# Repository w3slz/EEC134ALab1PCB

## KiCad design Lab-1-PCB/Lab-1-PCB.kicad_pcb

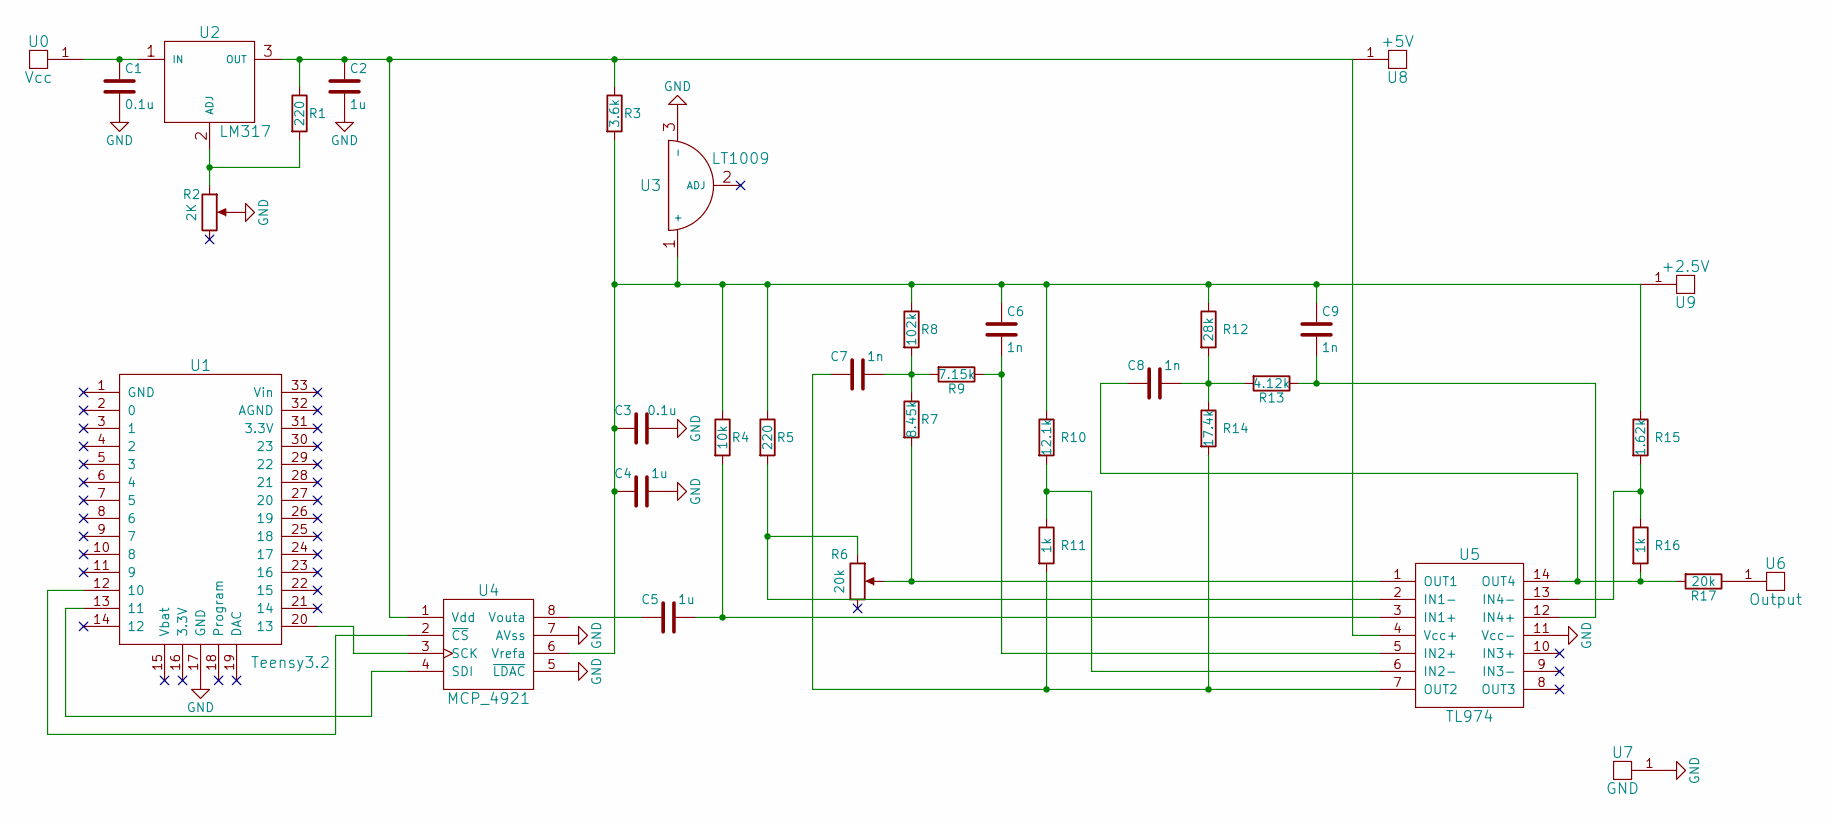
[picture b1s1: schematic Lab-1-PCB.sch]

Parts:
C1, C3: 0.1u; C_0805_HandSoldering
C2, C4, C5: 1u; C_0805_HandSoldering
C6, C7, C8, C9: 1n; C_0805_HandSoldering
R1, R5: 220; R_0805_HandSoldering
R2: 2K; CT-94EW
R3: 3.6k; R_0805_HandSoldering
R4: 10k; R_0805_HandSoldering
R6: 20k; CT-94EW
R7: 8.45k; R_0805_HandSoldering
R8: 102k; R_0805_HandSoldering
R9: 7.15k; R_0805_HandSoldering
R10: 12.1k; R_0805_HandSoldering
R11, R16: 1k; R_0805_HandSoldering
R12: 28k; R_0805_HandSoldering
R13: 4.12k; R_0805_HandSoldering
R14: 17.4k; R_0805_HandSoldering
R15: 1.62k; R_0805_HandSoldering
R17: 20k; R_0805_HandSoldering
U0: Vcc; Test_Point_Keystone_5000-5004_Miniature
U1: Teensy3.2
U2: LM317
U3: LT1009
U4: MCP_4921
U5: TL974
U6: Output; Test_Point_Keystone_5000-5004_Miniature
U7: GND; Test_Point_Keystone_5000-5004_Miniature
U8: +5V; Test_Point_Keystone_5000-5004_Miniature
U9: +2.5V; Test_Point_Keystone_5000-5004_Miniature

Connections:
GND: C1.2, C2.2, C3.2, C4.2, R2.2, U1.17 (GND), U3.3 (-), U4.5 (~LDAC), U4.7 (AVss), U5.11 (Vcc-), U7.1
unnamed: C1.1, U0.1, U2.1 (IN)
unnamed: C2.1, R1.1, R3.1, U2.3 (OUT), U4.1 (Vdd), U5.4 (Vcc+), U8.1
unnamed: C3.1, C4.1, C6.1, C9.1, R3.2, R4.1, R5.1, R8.1, R10.1, R12.1, R15.1, U3.1 (+), U4.6 (Vrefa), U9.1
unnamed: C5.1, U4.8 (Vouta)
unnamed: C5.2, R4.2, U5.3 (IN1+)
unnamed: C6.2, R9.1, U5.5 (IN2+)
unnamed: C7.1, R11.2, R14.2, U5.7 (OUT2)
unnamed: C7.2, R7.1, R8.2, R9.2
unnamed: C8.1, R16.2, R17.2, U5.14 (OUT4)
unnamed: C8.2, R12.2, R13.2, R14.1
unnamed: C9.2, R13.1, U5.12 (IN4+)
unnamed: R1.2, R2.1, U2.2 (ADJ)
unnamed: R5.2, R6.1, U5.2 (IN1-)
unnamed: R6.2, R7.2, U5.1 (OUT1)
unnamed: R10.2, R11.1, U5.6 (IN2-)
unnamed: R15.2, R16.1, U5.13 (IN4-)
unnamed: R17.1, U6.1
unnamed: U1.12 (10), U4.2 (~CS)
unnamed: U1.13 (11), U4.4 (SDI)
unnamed: U1.20 (13), U4.3 (SCK)

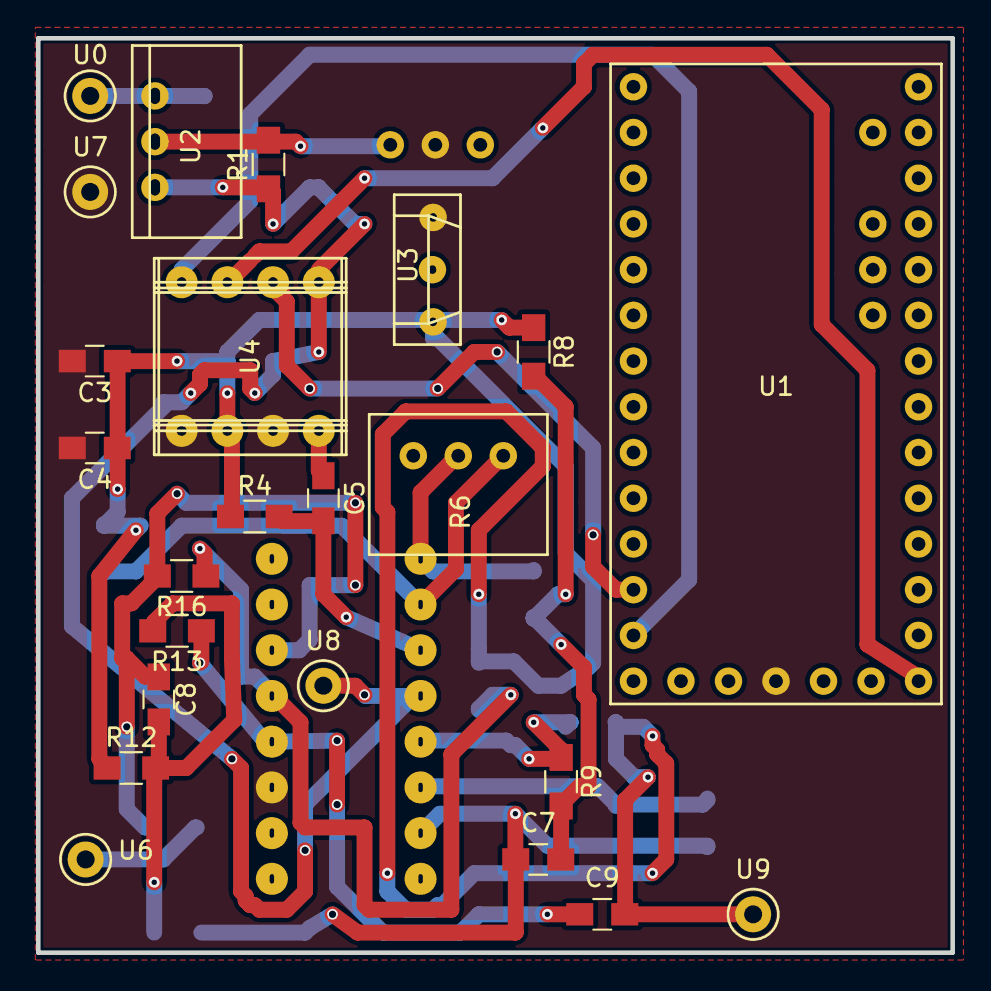
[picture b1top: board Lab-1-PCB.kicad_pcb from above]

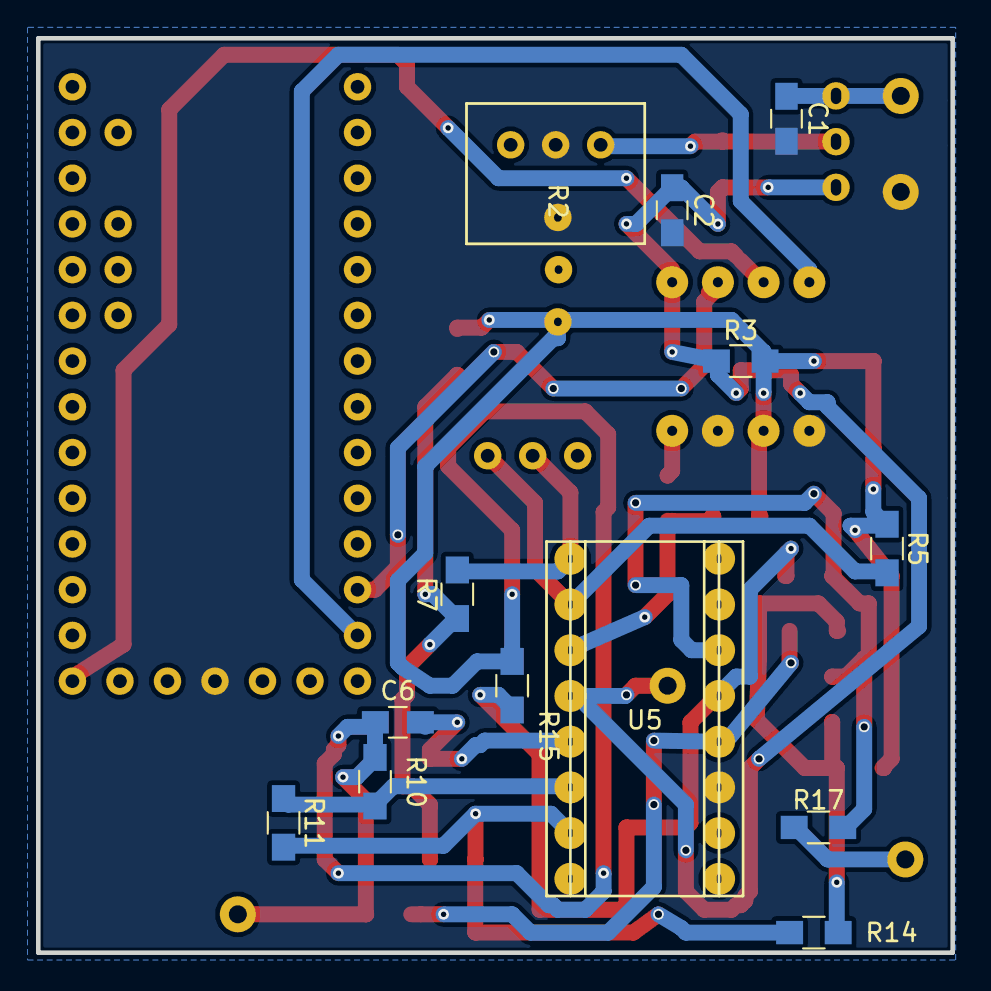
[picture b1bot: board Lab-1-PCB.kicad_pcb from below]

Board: 2 copper layers, 50.8 x 50.8 mm, 36 parts (13 on the bottom side), 21 nets.

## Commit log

2017-10-29 Upload
